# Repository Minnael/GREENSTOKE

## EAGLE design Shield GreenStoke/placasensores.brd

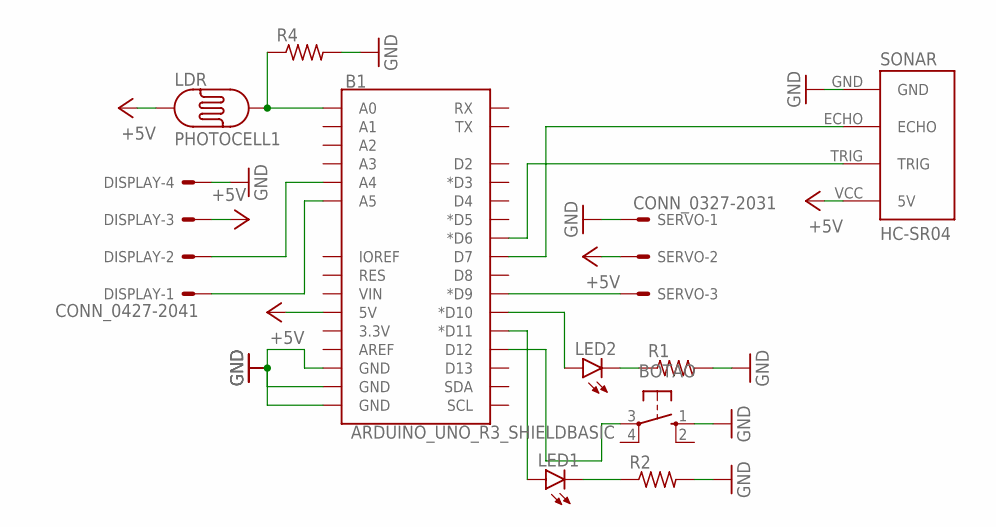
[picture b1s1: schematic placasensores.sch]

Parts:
B1: ARDUINO_UNO_R3_SHIELDBASIC; UNO_R3_SHIELD
BOTAO: 10-XX; B3F-10XX
DISPLAY: CONN_0427-2041; 6410-04
LDR: PHOTOCELL1; LDR_OFFBOARD
LED1, LED2: LED5MM
R1, R2, R4: R-US_0204/5; 0204/5
SERVO: CONN_0327-2031; 6410-03
SONAR: HC-SR04; HC-SR04_FOOTPRINT

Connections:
+5V: B1.5V, DISPLAY.3, LDR.1, SERVO.2, SONAR.VCC (5V)
GND: B1.GND@0 (GND), B1.GND@1 (GND), B1.GND@2 (GND), BOTAO.1 (S), DISPLAY.4, R1.2, R2.2, R4.2, SERVO.1, SONAR.GND
unnamed: B1.D12, BOTAO.3
unnamed: B1.D10 (*D10), LED2.A
unnamed: B1.D11 (*D11), LED1.A
unnamed: LED2.K (C), R1.1
unnamed: LED1.K (C), R2.1
unnamed: B1.A0, LDR.2, R4.1
unnamed: B1.D7, SONAR.ECHO
unnamed: B1.D6 (*D6), SONAR.TRIG
unnamed: B1.D9 (*D9), SERVO.3
unnamed: B1.A5, DISPLAY.1
unnamed: B1.A4, DISPLAY.2

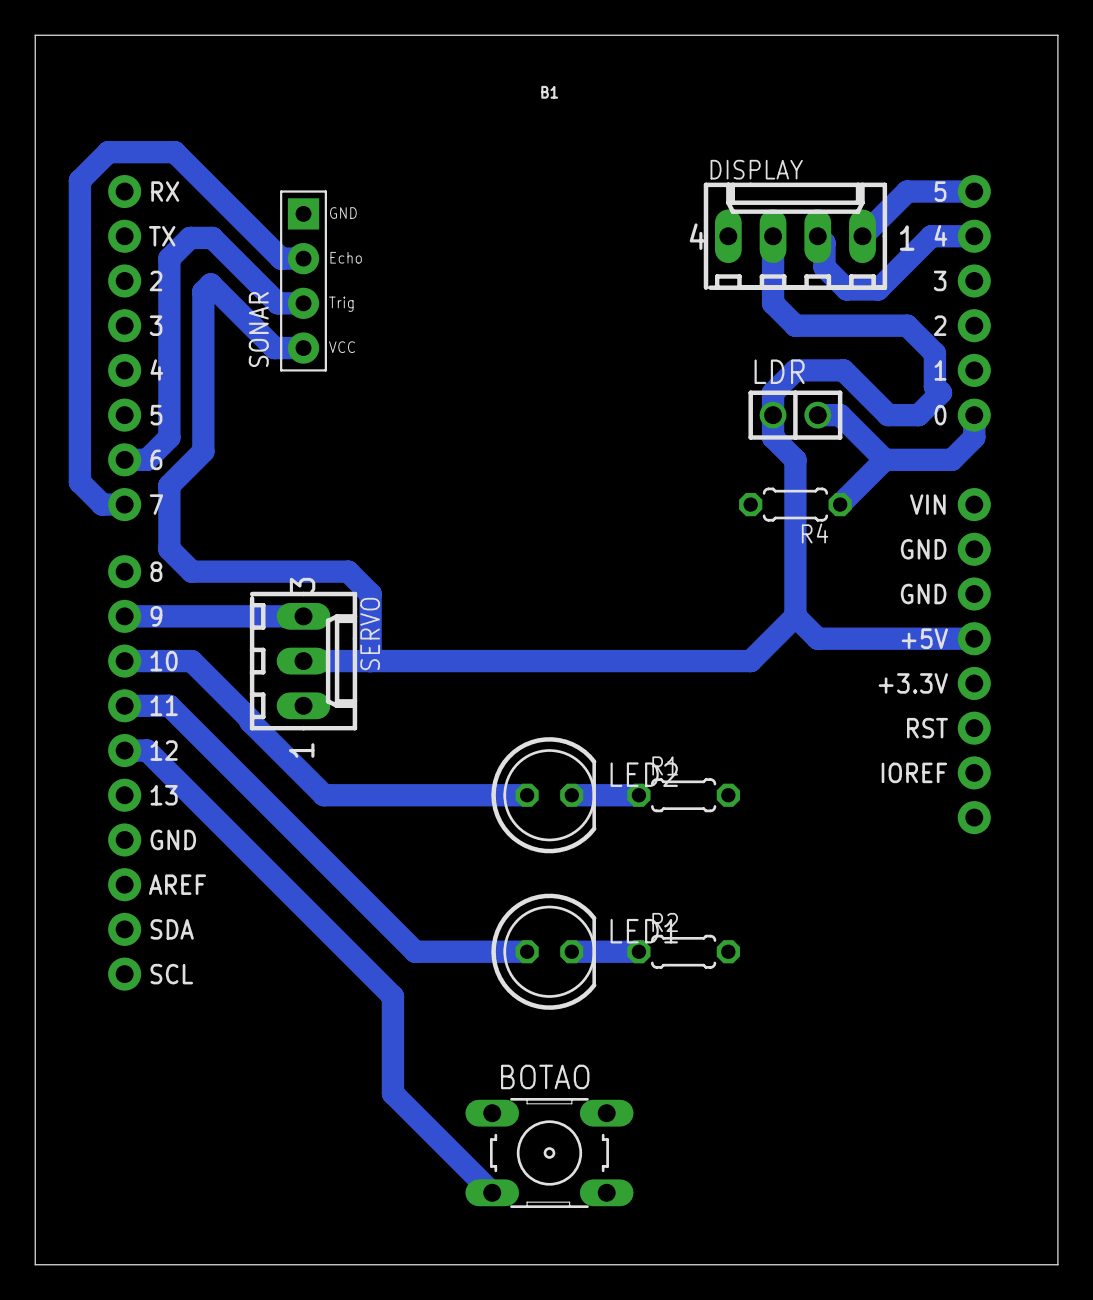
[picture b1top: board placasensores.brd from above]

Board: 2 copper layers, 58.1 x 69.8 mm, 11 parts (0 on the bottom side), 13 nets.
